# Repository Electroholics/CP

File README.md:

# Community Projects

## Lab Access Control System
Lab Access Control System

## Mess automation System
Mess Automation System

## Weather Station
Monitors Temperature and Humidity

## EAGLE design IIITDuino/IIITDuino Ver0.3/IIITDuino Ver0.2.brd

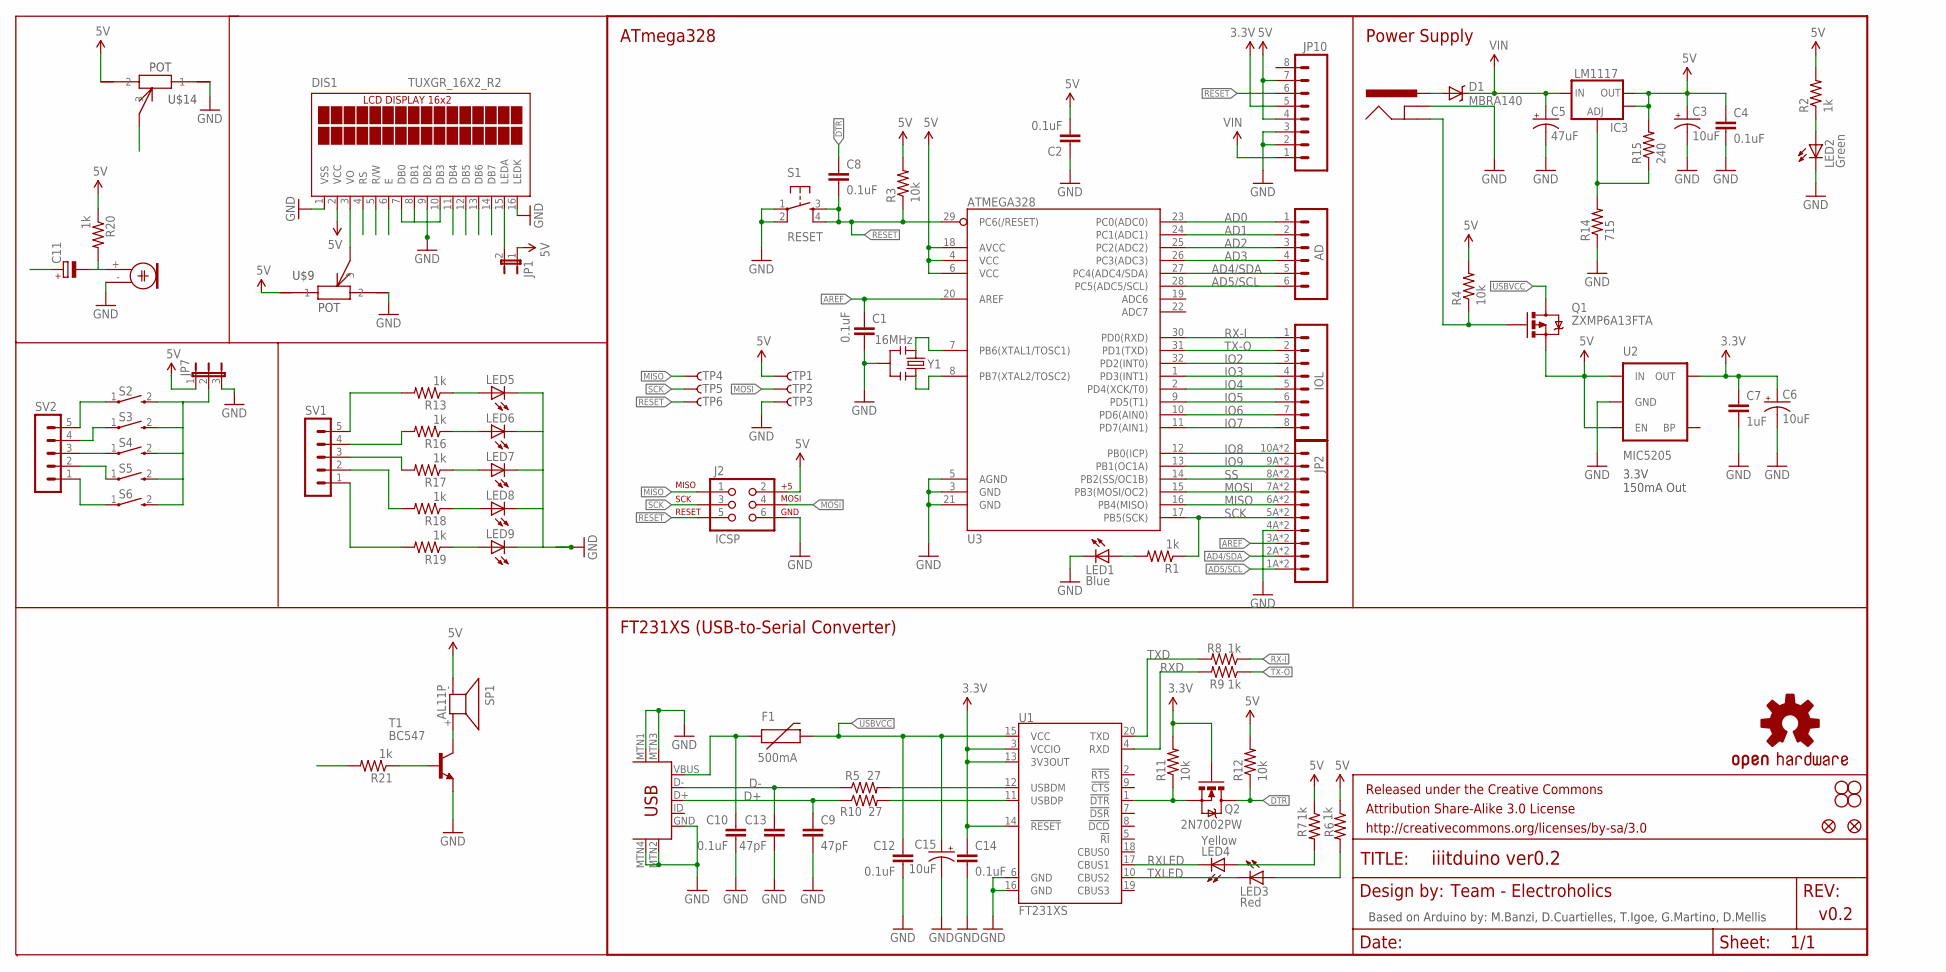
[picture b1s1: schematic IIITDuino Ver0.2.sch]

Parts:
AD: M06SMD-STRAIGHT-COMBO; 1X06_SMD_STRAIGHT_COMBO
C1, C2, C4, C8, C10, C12, C14: 0.1uF; 0603-CAP
C3, C6, C15: 10uF; EIA3216
C5: 47uF; PANASONIC_D
C7: 1uF; 0603-CAP
C9, C13: 47pF; 0603-CAP
C11: CPOL-EUE2.5-5; E2,5-5
D1: MBRA140; SMA-DIODE
DIS1: TUXGR_16X2_R2; LCD_16X2_PAC
F1: 500mA; PTC-1206
FRAME2: FRAME-LETTER; CREATIVE_COMMONS
IC3: LM1117; SOT223-ALT1
IOL: M08SMD-COMBO; 1X08_SMD_COMBINED
J1: POWER_JACKOVERPASTE_REDBOARD_0603; POWER_JACK_SMD_OVERPASTE_REDBOARD_0603
J2: ICSP; 2X3_SMT_POSTS
JP1: JP1E; JP1
JP2: M10SMD_COMBO; 1X10_SMD_COMBINED
JP3, JP4, JP5, JP6: STAND-OFF
JP7: JP2E; JP2
JP8, JP9: FIDUCIAL1X2; FIDUCIAL-1X2
JP10: M08SMD-COMBO; 1X08_SMD_COMBINED
LED1: Blue; LED-1206-NO_SILK
LED2: Green; LED-1206-NO_SILK
LED3: Red; LED-1206-NO_SILK
LED4: Yellow; LED-1206-NO_SILK
LED5, LED6, LED7, LED8, LED9: LEDCHIP-LED0805; CHIP-LED0805
M1: ELECTRET_MICROPHON-TOM-1545P-R; TOM-1545P-R
Q1: ZXMP6A13FTA; SOT23-3
Q2: 2N7002PW; SOT323
R1, R2, R6, R7, R8, R9, R13, R16, R17, R18, R19, R20, R21: 1k; 0603-RES
R3, R4, R11, R12: 10k; 0603-RES
R5, R10: 27; 0603-RES
R14: 715; 0603-RES
R15: 240; 0603-RES
S1: RESET; TACTILE_SWITCH_SMD
S2, S3, S4, S5, S6: 10-XX; B3F-10XX
SP1: AL11P
SV1, SV2: MA05-1
T1: BC547; TO92
TP1, TP2, TP3, TP4, TP5, TP6: TP-3x5; PAD.03X.05
U1: FT231XS; SSOP20_L
U2: MIC5205; SOT23-5
U3: ATMEGA328; TQFP32-08
U$9, U$14: POT; CA9V
U$13: USB-MINIB-5PIN; USB-MINIB
U$16: OSHW-LOGOS; OSHW-LOGO-S
Y1: 16MHz; RESONATOR-SMD

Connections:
3.3V: C6.A (+), C7.1, C14.1, JP10.5, Q2.1 (G), R11.2, U1.3 (VCCIO), U1.13 (3V3OUT), U1.14 (!RESET), U2.5 (OUT)
5V: C2.2, C3.A (+), C4.1, DIS1.2 (VCC), IC3.2 (OUT), IC3.4 (OUT), J2.2, JP1.1, JP10.4, JP10.7, Q1.2 (S), R2.2, R3.2, R4.2, R6.1, R7.1, R12.2, R15.2, R20.1, SP1.- (1), TP1.P$1, U2.1 (IN), U2.3 (EN), U3.4 (VCC), U3.6 (VCC), U3.18 (AVCC), U$9.A (1), U$14.K (2)
AD0: AD.1, U3.23 (PC0(ADC0))
AD1: AD.2, U3.24 (PC1(ADC1))
AD2: AD.3, U3.25 (PC2(ADC2))
AD3: AD.4, U3.26 (PC3(ADC3))
AD4/SDA: AD.5, JP2.2A (2), JP2.2B (2), U3.27 (PC4(ADC4/SDA))
AD5/SCL: AD.6, JP2.1A (1), JP2.1B (1), U3.28 (PC5(ADC5/SCL))
AREF: C1.1, JP2.3A (3), JP2.3B (3), U3.20 (AREF)
D+: C9.1, R10.1, U$13.D+
D-: C13.1, R5.1, U$13.D-
DTR: C8.1, Q2.3 (D), R12.1
GND: C1.2, C2.1, C3.C (-), C4.2, C5.-, C6.C (-), C7.2, C9.2, C10.2, C12.2, C13.2, C14.2, C15.C (-), DIS1.1 (VSS), DIS1.7 (DB0), DIS1.8 (DB1), DIS1.9 (DB2), DIS1.10 (DB3), DIS1.16 (LEDK), J1.GND (GNDBREAK), J2.6, JP2.4A (4), JP2.4B (4), JP10.2, JP10.3, LED1.C, LED2.C, LED5.C, LED6.C, LED7.C, LED8.C, LED9.C, M1.- (2), R14.1, S1.1, S1.2, T1.1 (E), TP3.P$1, U1.6 (GND), U1.16 (GND), U2.2 (GND), U3.3 (GND), U3.5 (AGND), U3.21 (GND), U$9.K (2), U$13.GND, U$13.MTN1 (MTN2), U$13.MTN2 (MTN3), U$13.MTN3 (MTN1), U$13.MTN4, U$14.A (1), Y1.2
INSERT: J1.P$4 (GND), Q1.1 (G), R4.1
IO2: IOL.3, U3.32 (PD2(INT0))
IO3: IOL.4, U3.1 (PD3(INT1))
IO4: IOL.5, U3.2 (PD4(XCK/T0))
IO5: IOL.6, U3.9 (PD5(T1))
IO6: IOL.7, U3.10 (PD6(AIN0))
IO7: IOL.8, U3.11 (PD7(AIN1))
IO8: JP2.10A (10), JP2.10B (10), U3.12 (PB0(ICP))
IO9: JP2.9A (9), JP2.9B (9), U3.13 (PB1(OC1A))
MISO: J2.1, JP2.6A (6), JP2.6B (6), TP4.P$1, U3.16 (PB4(MISO))
MOSI: J2.4, JP2.7A (7), JP2.7B (7), TP2.P$1, U3.15 (PB3(MOSI/OC2))
unnamed: LED1.A, R1.2
unnamed: LED2.A, R2.1
unnamed: U3.7 (PB6(XTAL1/TOSC1)), Y1.1
unnamed: U3.8 (PB7(XTAL2/TOSC2)), Y1.3
unnamed: DIS1.3 (VO), U$9.S (3)
unnamed: R5.2, U1.12 (USBDM)
unnamed: R10.2, U1.11 (USBDP)
unnamed: LED3.A, R6.2
unnamed: LED4.A, R7.2
unnamed: Q2.2 (S), R11.1, U1.1 (!DTR)
unnamed: IC3.1 (ADJ), R14.2, R15.1
unnamed: DIS1.15 (LEDA), JP1.2
unnamed: S2.1, SV2.5
unnamed: LED5.A, R13.1
unnamed: LED6.A, R16.1
unnamed: LED7.A, R17.1
unnamed: LED8.A, R18.1
unnamed: LED9.A, R19.1
unnamed: R13.2, SV1.5
unnamed: R16.2, SV1.4
unnamed: R17.2, SV1.3
unnamed: R18.2, SV1.2
unnamed: R19.2, SV1.1
unnamed: S3.1, SV2.4
unnamed: S4.1, SV2.3
unnamed: S5.1, SV2.2
unnamed: S6.1, SV2.1
unnamed: JP7.2, S2.2 (S), S3.2 (S), S4.2 (S), S5.2 (S), S6.2 (S)
unnamed: SP1.+ (2), T1.3 (C)
unnamed: C11.-, M1.+ (1), R20.2
unnamed: R21.1, T1.2 (B)
PWRIN: D1.A, J1.VIN0 (PWR)
RESET: C8.2, J2.5, JP10.6, R3.1, S1.3, S1.4, TP6.P$1, U3.29 (PC6(/RESET))
RX-I: IOL.1, R8.1, U3.30 (PD0(RXD))
RXD: R9.2, U1.4 (RXD)
RXLED: LED4.C, U1.17 (CBUS1)
SCK: J2.3, JP2.5A (5), JP2.5B (5), R1.1, TP5.P$1, U3.17 (PB5(SCK))
SS: JP2.8A (8), JP2.8B (8), U3.14 (PB2(SS/OC1B))
TX-O: IOL.2, R9.1, U3.31 (PD1(TXD))
TXD: R8.2, U1.20 (TXD)
TXLED: LED3.C, U1.10 (CBUS2)
USBVCC: C12.1, C15.A (+), F1.2, Q1.3 (D), U1.15 (VCC)
VIN: C5.+, D1.C, IC3.3 (IN), JP10.1
VUSB: C10.1, F1.1, U$13.VBUS

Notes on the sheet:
Power Supply
ATmega328
FT231XS (USB-to-Serial Converter)
Based on Arduino by: M.Banzi, D.Cuartielles, T.Igoe, G.Martino, D.Mellis
3.3V 150mA Out
Team - Electroholics
v0.2

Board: 2 copper layers, 91 parts (0 on the bottom side), 68 nets, no tracks yet.

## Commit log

2015-10-10 added folders
2015-10-22 added some links for reference
2015-11-02 Code and how to for LACS project
2015-11-07 Bug Fixes
2015-11-07 New Code Uploaded
2015-12-06 ver0.2 tushar commit
2015-12-07 Documented and added tutorials
2015-12-08 Added fritzing models
2015-12-08 Addition of images
2015-12-08 Repaired images and models
2015-12-09 Weather station 0.1
2015-12-16 Schematic
2016-01-03 ver 0.2 and 0.3 updated
2016-10-27 Updated WS

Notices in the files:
parts and their libraries:
SparkFun-Aesthetics: Licensing: CC v3.0 Share-Alike You are welcome to use this library for commercial purposes.
SparkFun-Aesthetics: Released under the Creative Commons Attribution Share-Alike 3.0 License
SparkFun-Aesthetics: http://creativecommons.org/licenses/by-sa/3.0
